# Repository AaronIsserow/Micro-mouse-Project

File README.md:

# Micro-mouse Project
This project consists of designing an autonomous maze solving robot. This robot is designed to autonomously navigate through a maze environment.
This repository contains the designs of the following two subsystems that are part of the micro-mouse system:
- The power subsystem
- The sensing subsystem

## Micro-Mouse Power Subsystem
The design and documentation for the power subsystem of a functional micro-mouse is provided. The project focuses on designing and manufacturing a power module that meets the specific requirements outlined in the project brief.
The power subsystem is one of several subsystems that make up the micro-mouse, and it is responsible for distributing power from the battery source to the rest of the system.

### Scope
The scope of this project includes:

- Designing and manufacturing a power module that adheres to the project requirements.
- Distributing power from the battery source to the motors and other components.
- Designing the module to accommodate charging from an external source.
- Ensuring the power module fits within the physical constraints of the micro-mouse.
- Testing the power module thoroughly before integration with the rest of the system.

## Micro-Mouse Sensing Subsystem

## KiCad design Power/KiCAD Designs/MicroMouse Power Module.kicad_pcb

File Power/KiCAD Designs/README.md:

# KiCAD Designs
This folder includes all design files including
- KiCAD project file
- KiCAD schematic file
- KiCAD pcb file
- Production Files
- Additional component libraries

## Production Files
This subfolder includes all files needed to manufacture the pcb from JLCPCB

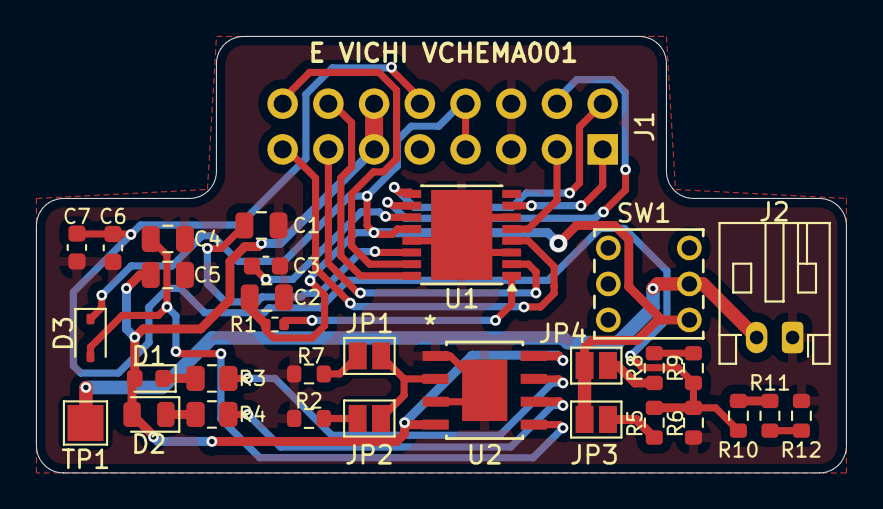
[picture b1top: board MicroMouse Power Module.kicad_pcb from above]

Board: 2 copper layers, 45.0 x 24.2 mm, 32 parts (1 on the bottom side), 29 nets.

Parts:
C1: 2.2u; C_0805_2012Metric
C2, C4, C5: 10u; C_0805_2012Metric
C3: 10n; C_0603_1608Metric
C6, C7: 1n; C_0603_1608Metric
D1: Charging LED (R); LED_0603_1608Metric
D2: Charged LED (G); LED_0805_2012Metric
D3: Discharge Current Blocked; D_SOD-323
J1: Electrical pinout; PinHeader_2x08_P2.54mm_Vertical
J2: Battery Pins; JST_PH_S2B-PH-K_1x02_P2.00mm_Horizontal
JP1, JP2, JP3, JP4: SolderJumper-2_P1.3mm_Open_Pad1.0x1.5mm
R1: 47k; R_0402_1005Metric
R2: 3k; R_0603_1608Metric
R3, R4: 1k; R_0805_2012Metric
R5, R6, R8, R10, R11, R12: 1M; R_0603_1608Metric
R7: 1.5k; R_0603_1608Metric
R9: 200k; R_0603_1608Metric
SW1: ON/OFF Switch; PS-5850A_GSW
TP1: Battery check; TestPoint_Pad_2.0x2.0mm
U1: DRV8833PWP; HTSSOP-16-1EP_4.4x5mm_P0.65mm_EP3.4x5mm
U2: TP4056; SOP8-PP_TPW

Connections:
+3.7V: C2.1, D3.1 (K), J1.7, J1.8, JP3.1 (A), JP4.2 (B), R1.1, SW1.6 (C), U1.12 (VM)
+5V: C5.1, D1.2 (A), D2.2 (A), J1.11, J1.12, U2.4 (VCC), U2.8 (CE)
/+: J2.2, SW1.5 (B), TP1.1
/BATT_ADC: C6.1, C7.1, J1.10, R5.1, R6.2, R9.1, R10.2
/Motor1_A: J1.13, U1.2 (AOUT1)
/Motor1_B: J1.15, U1.4 (AOUT2)
/Motor2_A: J1.1, U1.7 (BOUT1)
/Motor2_B: J1.3, U1.5 (BOUT2)
/PWM1: J1.2, U1.9 (BIN1)
/PWM2: J1.4, U1.10 (BIN2)
/PWM3: J1.14, U1.16 (AIN1)
/PWM4: J1.16, U1.15 (AIN2)
GND: C1.2, C2.2, C3.1, C4.2, C5.2, C6.2, C7.2, J1.5, J1.6, J2.1, R2.1, R6.1, R7.1, R12.1, U1.3 (AISEN), U1.6 (BISEN), U1.13 (GND), U1.17 (GND), U2.1 (TEMP), U2.3 (GND), U2.EPAD
unnamed: D1.1 (K), R3.2
unnamed: D2.1 (K), R4.2
unnamed: C4.1, D3.2 (A), U2.5 (BAT)
unnamed: JP1.1 (A), R7.2
unnamed: JP1.2 (B), JP2.2 (B), U2.2 (PROG)
unnamed: JP2.1 (A), R2.2
unnamed: JP3.2 (B), R5.2
unnamed: JP4.1 (A), R8.2
unnamed: R8.1, R9.2
unnamed: R10.1, R11.2
unnamed: R11.1, R12.2
unnamed: C3.2, U1.11 (VCP)
unnamed: C1.1, U1.14 (VINT)
unnamed: R1.2, U1.1 (~SLEEP)
unnamed: R3.1, U2.7 (*CHRG)
unnamed: R4.1, U2.6 (*STDBY)

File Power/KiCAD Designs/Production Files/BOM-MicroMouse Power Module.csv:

Comment,Designator,Footprint,LCSC
10u,"C2,C4,C5",C_0805_2012Metric,C15850
1n,"C6,C7",C_0603_1608Metric,C1588
1k,"R3,R4",R_0805_2012Metric,C17513
Discharge Current Blocked,D3,D_SOD-323,C191023
1.5k,R7,R_0603_1608Metric,C22843
Charging LED (R),D1,LED_0603_1608Metric,C2286
1M,"R10,R11,R12,R5,R6,R8",R_0603_1608Metric,C22935
Charged LED (G),D2,LED_0805_2012Metric,C2297
47k,R1,R_0402_1005Metric,C25792
200k,R9,R_0603_1608Metric,C25811
3k,R2,R_0603_1608Metric,C4211
DRV8833PWP,U1,HTSSOP-16-1EP_4.4x5mm_P0.65mm_EP3.4x5mm,C50506
TP4056,U2,SOP8-PP_TPW,C5311018
10n,C3,C_0603_1608Metric,C57112
ON/OFF Switch,SW1,PS-5850A_GSW,C963201
2.2u,C1,C_0805_2012Metric,

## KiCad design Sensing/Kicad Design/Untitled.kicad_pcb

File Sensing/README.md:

This project develops the sensing part of a micro-mouse robot that's meant to move through mazes on its own. The main job of this subsystem is to help the robot spot obstacles, which lets it make quick decisions to find its way to the end of the maze efficiently. I will be working on both the hardware and software needed to detect obstacles and guide the robot.

The importance of this project lies in its role in the robot's ability to navigate by itself using IR light. By figuring out where obstacles are, the robot can understand its surroundings better. 

This project is looked after by me, Aaron Isserow, with help from another student, Emanuele Vichi. We're always open to new ideas and improvements, so feel free to chip in if you're interested in making the project better.

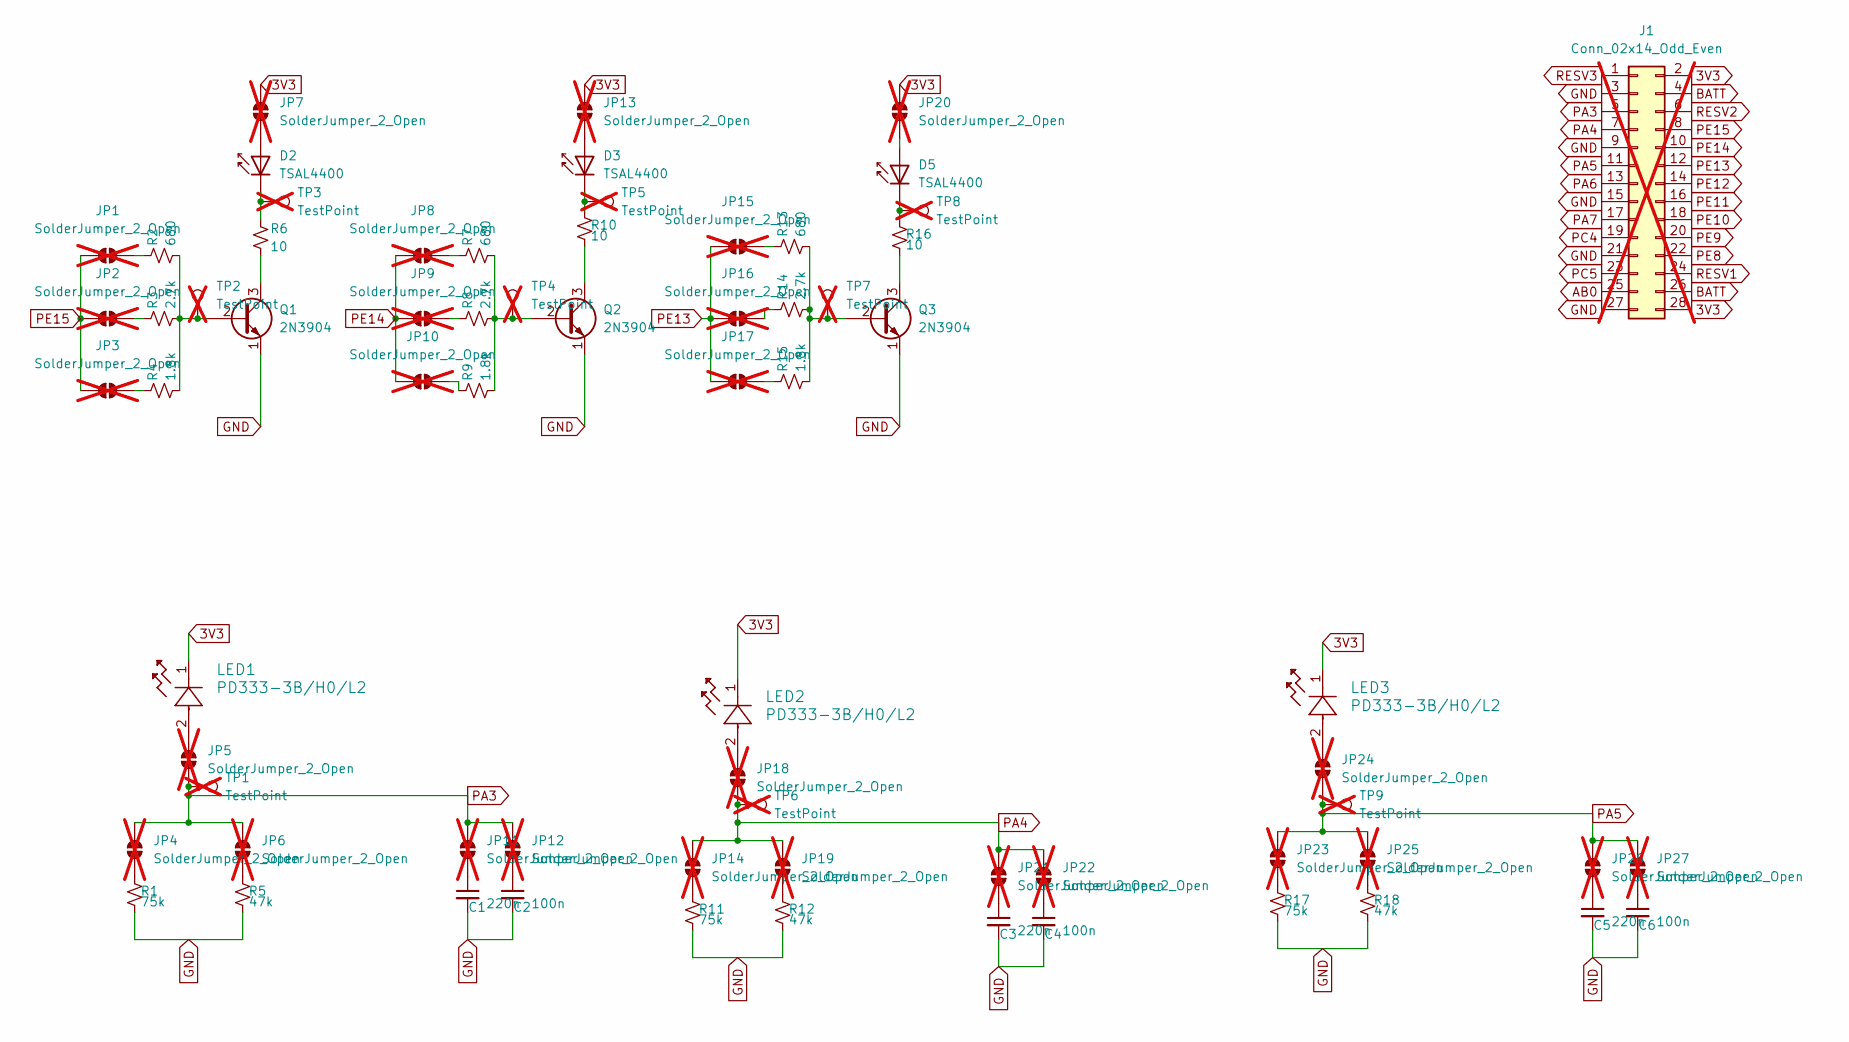
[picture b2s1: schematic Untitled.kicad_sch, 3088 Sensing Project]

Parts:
C1, C3, C5: 220n; C_0805_2012Metric; LCSC C5378
C2, C4, C6: 100n; C_0402_1005Metric; LCSC C307331
D2, D3, D5: TSAL4400; LED_D3.0mm_IRBlack; LCSC C94135
J1: Conn_02x14_Odd_Even; PinHeader_2x14_P2.54mm_Vertical; not fitted
JP1, JP2, JP3, JP4, JP5, JP6, JP7, JP8, JP9, JP10, JP11, JP12, JP13, JP14, JP15, JP16, JP17, JP18, JP19, JP20, JP21, JP22, JP23, JP24, JP25, JP26, JP27: SolderJumper_2_Open; SolderJumper-2_P1.3mm_Open_Pad1.0x1.5mm; not fitted
LED1, LED2, LED3: PD333-3B/H0/L2; LED_PD333_EVE; LCSC C264286
Q1, Q2, Q3: 2N3904; TO-92_Inline; LCSC C2874602
R1, R11, R17: 75k; R_0603_1608Metric; LCSC C23242
R2, R7, R13: 680; R_0603_1608Metric; LCSC C23228
R3, R8, R14: 2.7k; R_0805_2012Metric; LCSC C17530
R4, R9, R15: 1.8k; R_0603_1608Metric; LCSC C4177
R5, R12, R18: 47k; R_0603_1608Metric; LCSC C25819
R6, R10, R16: 10; R_0402_1005Metric; LCSC C25077
TP1, TP2, TP3, TP4, TP5, TP6, TP7, TP8, TP9: TestPoint; TestPoint_Pad_D2.0mm; not fitted

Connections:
3V3: J1.2, J1.28, JP7.1 (A), JP13.1 (A), JP20.1 (A), LED1.1, LED2.1, LED3.1
AB0: J1.25
BATT: J1.4, J1.26
GND: C1.2, C2.2, C3.2, C4.2, C5.2, C6.2, J1.3, J1.9, J1.15, J1.21, J1.27, Q1.1 (E), Q2.1 (E), Q3.1 (E), R1.2, R5.2, R11.2, R12.2, R17.2, R18.2
unnamed: D2.2 (A), JP7.2 (B)
unnamed: D2.1 (K), R6.1, TP3.1
unnamed: D3.2 (A), JP13.2 (B)
unnamed: D3.1 (K), R10.1, TP5.1
unnamed: D5.2 (A), JP20.2 (B)
unnamed: D5.1 (K), R16.1, TP8.1
unnamed: JP1.1 (A), R2.1
unnamed: JP2.1 (A), R3.1
unnamed: JP3.1 (A), R4.1
unnamed: JP4.1 (A), R1.1
unnamed: JP5.1 (A), LED1.2
unnamed: JP6.1 (A), R5.1
unnamed: JP8.1 (A), R7.1
unnamed: JP9.1 (A), R8.1
unnamed: JP10.1 (A), R9.1
unnamed: C1.1, JP11.1 (A)
unnamed: C2.1, JP12.1 (A)
unnamed: JP14.1 (A), R11.1
unnamed: JP15.1 (A), R13.1
unnamed: JP16.1 (A), R14.1
unnamed: JP17.1 (A), R15.1
unnamed: JP18.1 (A), LED2.2
unnamed: JP19.1 (A), R12.1
unnamed: C3.1, JP21.1 (A)
unnamed: C4.1, JP22.1 (A)
unnamed: JP23.1 (A), R17.1
unnamed: JP24.1 (A), LED3.2
unnamed: JP25.1 (A), R18.1
unnamed: C5.1, JP26.1 (A)
unnamed: C6.1, JP27.1 (A)
unnamed: Q1.2 (B), R2.2, R3.2, R4.2, TP2.1
unnamed: Q1.3 (C), R6.2
unnamed: Q2.2 (B), R7.2, R8.2, R9.2, TP4.1
unnamed: Q2.3 (C), R10.2
unnamed: Q3.2 (B), R13.2, R14.2, R15.2, TP7.1
unnamed: Q3.3 (C), R16.2
PA3: J1.5, JP4.2 (B), JP5.2 (B), JP6.2 (B), JP11.2 (B), JP12.2 (B), TP1.1
PA4: J1.7, JP14.2 (B), JP18.2 (B), JP19.2 (B), JP21.2 (B), JP22.2 (B), TP6.1
PA5: J1.11, JP23.2 (B), JP24.2 (B), JP25.2 (B), JP26.2 (B), JP27.2 (B), TP9.1
PA6: J1.13
PA7: J1.17
PC4: J1.19
PC5: J1.23
PE8: J1.22
PE9: J1.20
PE10: J1.18
PE11: J1.16
PE12: J1.14
PE13: J1.12, JP15.2 (B), JP16.2 (B), JP17.2 (B)
PE14: J1.10, JP8.2 (B), JP9.2 (B), JP10.2 (B)
PE15: J1.8, JP1.2 (B), JP2.2 (B), JP3.2 (B)
RESV1: J1.24
RESV2: J1.6
RESV3: J1.1

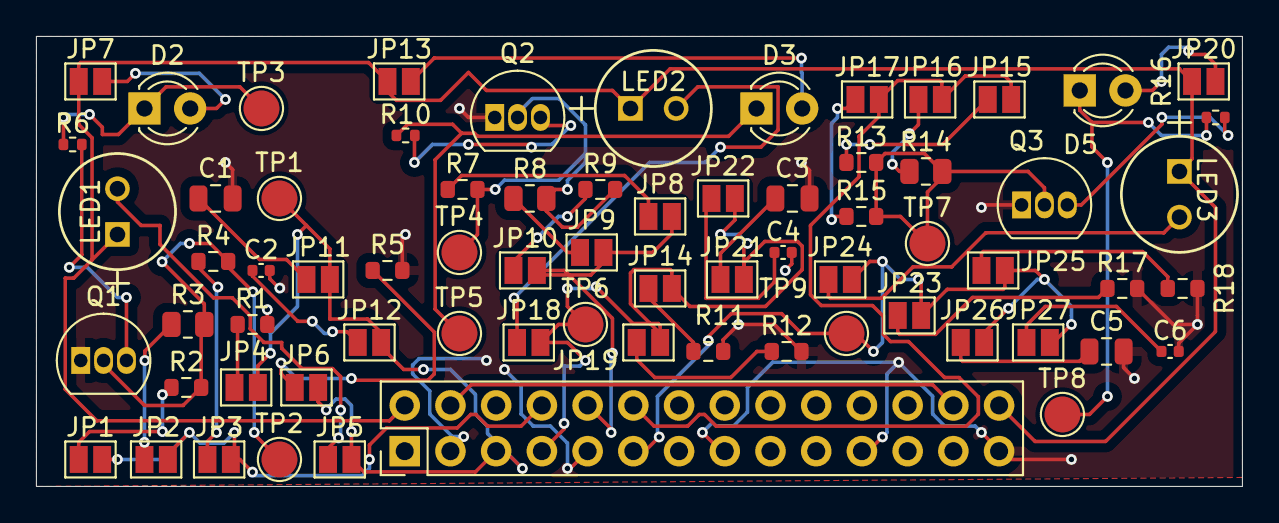
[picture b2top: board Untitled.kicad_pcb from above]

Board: 2 copper layers, 67.0 x 25.0 mm, 70 parts (0 on the bottom side), 45 nets.

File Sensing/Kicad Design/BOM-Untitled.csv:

Comment,Designator,Footprint,LCSC
2.7k,"R14,R3,R8",R_0805_2012Metric,C17530
680,"R13,R2,R7",R_0603_1608Metric,C23228
75k,"R1,R11,R17",R_0603_1608Metric,C23242
10,"R10,R16,R6",R_0402_1005Metric,C25077
47k,"R12,R18,R5",R_0603_1608Metric,C25819
PD333-3B/H0/L2,"LED1,LED2,LED3",LED_PD333_EVE,C264286
2N3904,"Q1,Q2,Q3",TO-92_Inline,C2874602
100n,"C2,C4,C6",C_0402_1005Metric,C307331
1.8k,"R15,R4,R9",R_0603_1608Metric,C4177
220n,"C1,C3,C5",C_0805_2012Metric,C5378
TSAL4400,"D2,D3,D5",LED_D3.0mm_IRBlack,C94135

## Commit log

2024-04-09 Create ggg
2024-04-09 Create fff
2024-04-11 Create Datasheets
2024-04-11 Create aaa
2024-04-11 Rename 0900766b815381bf.pdf to 2N3904.pdf
2024-04-11 Rename 0900766b80dea07c.pdf to TSAL4400.pdf
2024-04-21 Rename Power/DRV8833PWPR.pdf to Power/Datasheets/DRV8833PWPR.pdf
2024-04-21 Rename Power/G-Switch-PS-5850A-6PL.pdf to Power/Datasheets/G-Switch-PS-5850A-6PL.pdf
2024-04-21 Rename Power/TP4056.pdf to Power/Datasheets/TP4056.pdf
2024-04-21 Rename Power/KiCAD Designs/GERBER-MicroMouse Power Module.zip to Power/KiCAD Designs/Production Files/GERBER-MicroMouse Power Module.zip
2024-04-21 Rename EEE3088F_2024_project_description_v13.pdf to Project Description
2024-04-21 Rename Project Description to EEE3088F_2024_project_description_v13.pdf
